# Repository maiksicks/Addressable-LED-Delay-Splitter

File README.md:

# Addressable LED Delay Splitter (WS2812B / SK6812)

This project implements a "delay splitter" for addressable LED strips (WS2812B / SK6812) using an [ATtiny406](https://www.microchip.com/en-us/product/attiny406) microcontroller.
The device should work for all 800 kHz LED strips that only use one data line.

> Inspired by [WS2812B Delay Splitter](https://hackaday.io/project/8181-ws2812b-delay-splitter) that uses a [CMIC](https://en.wikipedia.org/wiki/Configurable_mixed-signal_IC) for this task.

> [!NOTE]
> More images are available in the [Gallery](./docs/Gallery.md). Including a short demo video showing the device in action.

## Description

The splitter takes a single LED data stream as input and provides two outputs:

- **Primary output**: This channel outputs the first N pixels of the input stream, where N is the configured pixel number.

- **Secondary output**: This channel outputs the remaining pixels of the input stream after the first N pixels.

### Basic use-case

- `pixel delay = 3`
    ```
                                 +- (1) - (2) - (3)
    [Controller] --- [Splitter] -+
                                 +- (4) - (5) - (6)
    ```

- `pixel delay = 3` and `primary passthrough = on`
    ```
                                 +- (1) - (2) - (3) - (4) - (5) - (6)
    [Controller] --- [Splitter] -+
                                 +- (4) - (5) - (6)
    ```

- Chaining
    ```
                                 +- (1) - (2) - (3)
    [Controller] --- [Splitter] -+
                                 +- [Splitter] ...
    ```
    ```
    [Controller] --- (1) - (2) - (3) --- [Splitter] ...
    ```

### How it works

Due to the high frequency of the WS2812B protocol (800kHz, 1.25µs per bit), the splitter uses many hardware features of the ATtiny406 to achieve the required timing:

- **Event System**
  Distribute the different signals (data input and control pin) to the various peripherals w(mostly) without CPU intervention.

- **CCL (Configurable Custom Logic)**
  Look-up tables (LUTs) are used to asynchronously route the input data stream to the outputs.

  - `Output_1 = Input_1 AND NOT Control_Pin`
  - `Output_2 = Input_1 AND Control_Pin`

- **TCA0 (Bit Counter)**
  Counts the number of bits / rising edges / events received via the event system. When the configured number of bits (delay) is reached, the control pin is switched to route the data to output 2.

- **TCB0 (Timeout Timer)**
  When the control pin is switched to output 2, this timer is started. If no rising edges are detected for a certain amount of time (indicating the reset condition of the WS2812B), the control pin is switched back to output 1.

## Configuration

The device can be configured via jumpers or by hardcoding values in `config.hpp`.

### Jumper configuration

There are 8 jumpers available to configure the pixel delay. The delay can be set from 0 to 255 pixels.

There is an additional jumper to change from RGB mode (24 bits per pixel) to RGBW mode (32 bits per pixel).

### Hardcoded configuration

The following parameters can be hardcoded in `config.hpp`:

- `PIXEL_DELAY` - Number of pixels to delay the output
- `RGBW_MODE` - Enable RGBW mode (32 bits per pixel instead of 24)
- `BITS_PER_PIXEL` - Number of bits per pixel (24 for RGB, 32 for RGBW)
- `SWAP_OUTPUTS` - Swap the primary and secondary outputs (output 1 and output 2)
- `PRIMARY_OUTPUT_PASSTHROUGH` - Enable passthrough of the primary output. When enabled, the primary output will not be turned off when the secondary output is active.
- `DISABLE_OUTPUT_1` and `DISABLE_OUTPUT_2` - Self-explanatory :)
- `LED_RESET_TIMEOUT` - Duration (in microseconds) to detect the reset condition of the WS2812B. The default is 50µs, which is a safe value for up to ~800kHz data rates.

Special parameters:

- `FORCE_SHORTED_CONTROL_PIN` - Forces the _shorted configuration pin mode_ to be enabled. This mode will be automatically enabled if jumper "128" is used. The control signal will then be inverted internally instead of setting the pin HIGH and LOW. 
  _Background: This mode had to be introduced because the hardware design of the splitter (revision 1) already had all Port B pins used for the configuration jumpers. The Event System only supports Port B pins as event generators on `ASYNCCH1`._

### Operation voltage

The device contains an onboard voltage regulator that can accept input voltages up to 30V (absolute maximum rating). Therefore, the recommend input voltages are 12V and 24V.

It is also possible to power the device with 5V. However, in this case, the voltage regulator will not be able to provide a stable 5V output for the ATtiny406. It may be a good idea to remove the voltage regulator and connect the 5V pin directly to the VCC pin.

### Flashing

The project can be built and flashed using [PlatformIO](https://platformio.org/).

For flashing, an UPDI programmer is required. 
You can also build a simple UPDI programmer using an Arduino Uno/Nano with ATmega328P:

1. Download the [jtag2updi repository](https://github.com/ElTangas/jtag2updi).
2. Rename the `source` folder to `jtag2updi` (otherwise Arduino IDE will not open it).
3. Open the `jtag2updi.ino` file using the Arduino IDE.
4. Connect the Arduino, select the correct board and port in the Arduino IDE, and upload the sketch.

After this, you can connect pin 6 of the Arduino to the UPDI pin of the ATtiny406, and use PlatformIO to flash the splitter firmware.

## Limitations

There is a maximum amount of leds that can be connected to a single data line. This limit is determined by the data rate of the LEDs. The formula to calculate the maximum number of LEDs is:

`N = ( (1 / f) - T_reset ) / ( B / R )`

Where:
- `N` = maximum number of LEDs
- `f` = frames per second (e.g. 60Hz)
- `T_reset` = reset time of the LEDs (e.g. 50µs)
- `B` = bits per pixel (e.g. 24 for RGB, 32 for RGBW)
- `R` = data rate in bits per second (e.g. 800,000 bps)

Example:
- With 60 Hz and RGB LEDs: up to 553 LEDs
- With 60 Hz and RGBW LEDs: up to 415 LEDs

- With 30 Hz and RGB LEDs: up to 1109 LEDs
- With 30 Hz and RGBW LEDs: up to 832 LEDs

## Ordering PCBs

Read the [README](./kicad/Addressable_LED_Delay_Splitter/README.md) in the `kicad` folder for details on the PCB design and order.

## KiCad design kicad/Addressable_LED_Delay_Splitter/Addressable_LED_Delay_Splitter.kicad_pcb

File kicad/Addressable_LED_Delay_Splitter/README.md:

# Addressable LED Delay Splitter (PCB)

This folder contains the [KiCad](https://kicad.org/) project for the Addressable LED Delay Splitter PCB.

## Production files

Production files can be found in the `jlcpcb/production_files` folder.
These files were generated by the [KiCAD JLCPCB tools plugin](https://github.com/bouni/kicad-jlcpcb-tools).

It should be possible to upload the GERBER archive to other PCB manufacturers as well, but this has not been tested.

The BOM and CPL files are in the format required by [JLCPCB](https://jlcpcb.com/).

It may be required to check and adjust the part numbers before ordering, because parts are from time to time replaced or go out of stock.

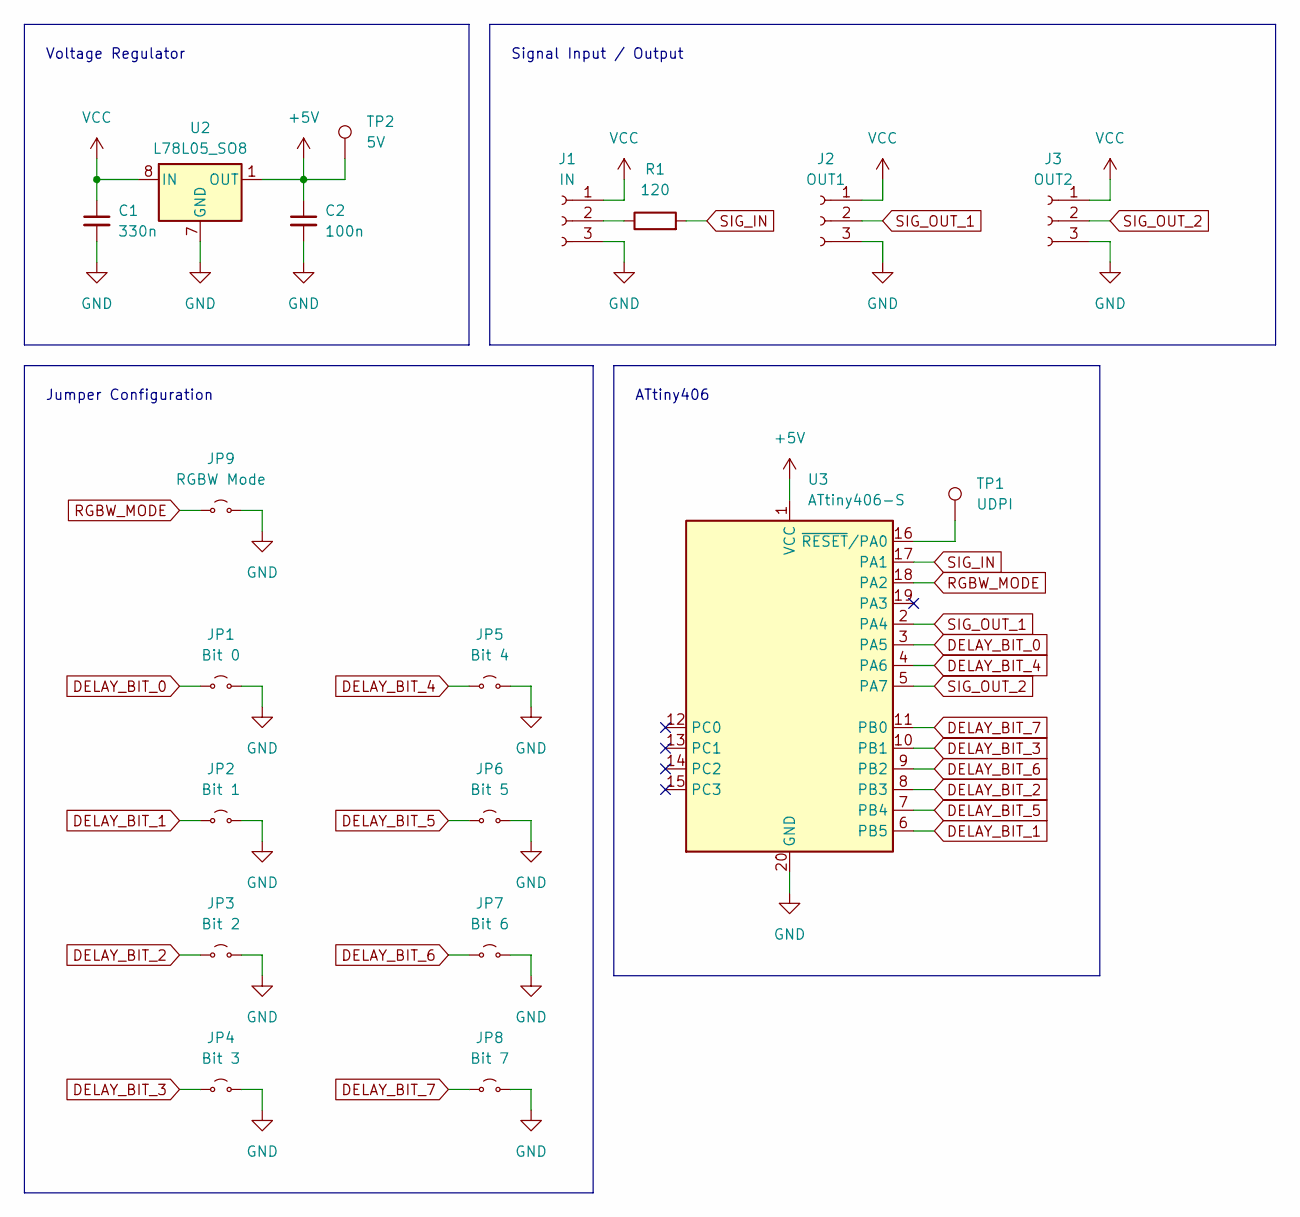
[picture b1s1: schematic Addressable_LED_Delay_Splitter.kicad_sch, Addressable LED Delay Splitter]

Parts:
C1: 330n; C_0805_2012Metric; LCSC C49678
C2: 100n; C_0805_2012Metric; LCSC C13967
J1: IN; ARGB_Solder_Header
J2: OUT1; ARGB_Solder_Header
J3: OUT2; ARGB_Solder_Header
JP1: Bit 0; SolderJumper-2_P1.3mm_Open_RoundedPad1.0x1.5mm
JP2: Bit 1; SolderJumper-2_P1.3mm_Open_RoundedPad1.0x1.5mm
JP3: Bit 2; SolderJumper-2_P1.3mm_Open_RoundedPad1.0x1.5mm
JP4: Bit 3; SolderJumper-2_P1.3mm_Open_RoundedPad1.0x1.5mm
JP5: Bit 4; SolderJumper-2_P1.3mm_Open_RoundedPad1.0x1.5mm
JP6: Bit 5; SolderJumper-2_P1.3mm_Open_RoundedPad1.0x1.5mm
JP7: Bit 6; SolderJumper-2_P1.3mm_Open_RoundedPad1.0x1.5mm
JP8: Bit 7; SolderJumper-2_P1.3mm_Open_RoundedPad1.0x1.5mm
JP9: RGBW Mode; SolderJumper-2_P1.3mm_Open_RoundedPad1.0x1.5mm
R1: 120; R_0805_2012Metric; LCSC C17437
TP1: UDPI; TestPoint_Pad_D1.0mm
TP2: 5V; TestPoint_Pad_D1.0mm
U2: L78L05_SO8; SOIC-8_3.9x4.9mm_P1.27mm; LCSC C7543
U3: ATtiny406-S; SOIC-20W_7.5x12.8mm_P1.27mm; LCSC C1338099

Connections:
+5V: C2.1, TP2.1, U2.1 (OUT), U3.1 (VCC)
DELAY_BIT_0: JP1.1 (A), U3.3 (PA5)
DELAY_BIT_1: JP2.1 (A), U3.6 (PB5)
DELAY_BIT_2: JP3.1 (A), U3.8 (PB3)
DELAY_BIT_3: JP4.1 (A), U3.10 (PB1)
DELAY_BIT_4: JP5.1 (A), U3.4 (PA6)
DELAY_BIT_5: JP6.1 (A), U3.7 (PB4)
DELAY_BIT_6: JP7.1 (A), U3.9 (PB2)
DELAY_BIT_7: JP8.1 (A), U3.11 (PB0)
GND: C1.2, C2.2, J1.3, J2.3, J3.3, JP1.2 (B), JP2.2 (B), JP3.2 (B), JP4.2 (B), JP5.2 (B), JP6.2 (B), JP7.2 (B), JP8.2 (B), JP9.2 (B), U2.2 (GND), U2.3 (GND), U2.6 (GND), U2.7 (GND), U3.20 (GND)
unnamed: J1.2, R1.1
unnamed: TP1.1, U3.16 (~RESET/PA0)
RGBW_MODE: JP9.1 (A), U3.18 (PA2)
SIG_IN: R1.2, U3.17 (PA1)
SIG_OUT_1: J2.2, U3.2 (PA4)
SIG_OUT_2: J3.2, U3.5 (PA7)
VCC: C1.1, J1.1, J2.1, J3.1, U2.8 (IN)

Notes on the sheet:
ATtiny406
Signal Input / Output
Voltage Regulator
Jumper Configuration

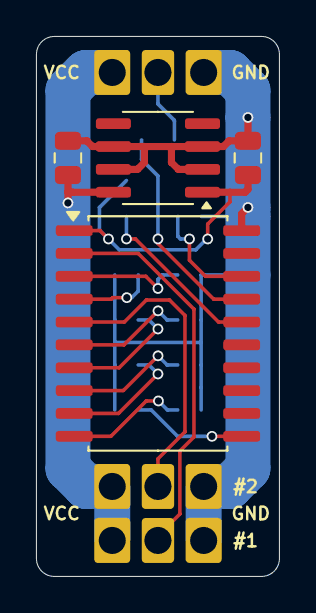
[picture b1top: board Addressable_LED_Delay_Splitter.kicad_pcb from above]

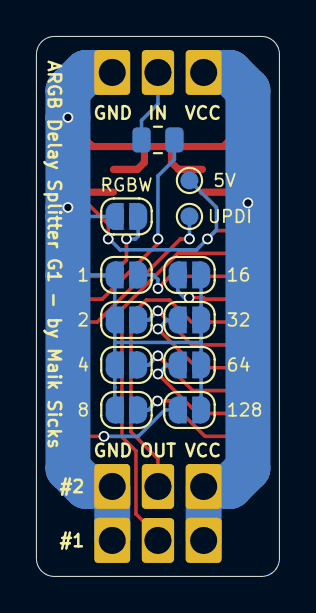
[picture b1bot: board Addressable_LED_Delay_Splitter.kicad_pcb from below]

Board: 2 copper layers, 13.5 x 30.0 mm, 19 parts (12 on the bottom side), 17 nets.

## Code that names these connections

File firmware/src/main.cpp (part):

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 * WS2812B Signal Splitter for ATTiny406
 *
 * Splits an incoming WS2812B signal into two outputs based on pixel count.
 * - First N pixels go to Output 1 (PA4 / LUT0-OUT)
 * - Remaining pixels go to Output 2 (PA7 / LUT1-OUT)
 */


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 * Reads configuration from GPIO pins if READ_CONFIG_FROM_JUMPERS is defined,
 * otherwise uses hardcoded values.
 *
 * Also detects if PB0 is shorted to ground and adjusts control logic accordingly.
 *
 * Delay pixel count (8-bit value):
 *   PA5: Bit 0 (LSB)
 *   PB5: Bit 1
 *   PB3: Bit 2
 *   PB1: Bit 3
 *   PA6: Bit 4
 *   PB4: Bit 5
 *   PB2: Bit 6
 *   PB0: Bit 7 (MSB)
 *
 * RGBW mode:
 *   PA2: RGBW enable (1 = 32 bits/pixel, 0 = 24 bits/pixel)
 *
 * Pins are read with pull-ups enabled:
 *   - Grounded pin = 1 (jumper installed)
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    // Small delay to let pull-ups stabilize
    _delay_us(100);

    // Read RGBW mode from PA2
    bool rgbw_mode = !(PORTA.IN & PIN2_bm);

    if (rgbw_mode) {
      bits_per_pixel = BITS_PER_PIXEL_RGBW;
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    if (!(PORTB.IN & PIN0_bm)) pixel_delay |= (1 << 7);  // Bit 7

    #ifndef FORCE_SHORTED_CONTROL_PIN
      // Check if PB0 is shorted to ground
      if (pixel_delay & (1 << 7)) {
        controlPinShorted = true;
      }
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    // Use hardcoded configuration values

    #ifndef FORCE_SHORTED_CONTROL_PIN
      // Check if PB0 is shorted to ground by configuring it as input with pull-up and reading its state
      PORTB.DIRCLR = PIN0_bm;
      PORTB.PIN0CTRL = PORT_PULLUPEN_bm;

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 * Configure GPIO pins
 */
void setupPins() {
  // PA1: Input (WS2812B data input)
  PORTA.DIRCLR = PIN1_bm;

  // PA4 and PA7 direction is controlled by CCL when OUTEN is enabled
  // But we set them as outputs for clarity
  PORTA.DIRSET = PIN4_bm | PIN7_bm;

  // PB0: Control pin for output switching
  if (controlPinShorted) {
    // Use PB0 as input. Toggle invert flag to trigger events.
    PORTB.DIRCLR = PIN0_bm;
  } else {
    // Use PB0 as output. Toggle output to trigger events.
    PORTB.DIRSET = PIN0_bm;
    PORTB.OUTSET = PIN0_bm;
  }
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/**
 * Configure the Event System
 *
 * Routes PA1 signal to:
 * - Both LUTs via Async Event Channel 0 (for signal buffering)
 * - TCA0 via Sync Event Channel 0 (for hardware bit counting)
 *
 * Routes PB0 signal to:
 * - Both LUTs via Async Event Channel 1 (for output control)
 */
void setupEventSystem() {
  // Async Channel 0: PA1 (data signal) for both LUTs
  EVSYS.ASYNCCH0 = EVSYS_ASYNCCH0_PORTA_PIN1_gc;

  // Async Channel 1: PB0 (control signal) for both LUTs
  EVSYS.ASYNCCH1 = EVSYS_ASYNCCH1_PORTB_PIN0_gc;

  // Route Async Channel 0 to both LUT0 and LUT1 Event 0 inputs
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  EVSYS.ASYNCUSER4 = EVSYS_ASYNCUSER4_ASYNCCH1_gc;  // LUT0 E1 <- CH1 (control)
  EVSYS.ASYNCUSER5 = EVSYS_ASYNCUSER5_ASYNCCH1_gc;  // LUT1 E1 <- CH1 (control)

  // Sync Channel 0: PA1 (data signal) for TCA0
  EVSYS.SYNCCH0 = EVSYS_SYNCCH0_PORTA_PIN1_gc;

  // Route Sync Channel 0 to TCA0 for event counting
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 * Configure the CCL (Configurable Custom Logic)
 *
 * Two LUTs are configured to control the outputs based on the data and control signals:
 * - LUT0 controls Output 1 (PA4)
 * - LUT1 controls Output 2 (PA7)
 *
 * Both LUTs use the same inputs:
 * - Input 0: Event 0 (data signal from PA1)
 * - Input 1: Event 1 (control signal from PB0)
 * - Input 2: Masked (forced to 0)
 */
void setupCCL() {
  // Disable CCL while configuring
  CCL.CTRLA = 0;

  // LUT0 Configuration (Output 1 - PA4)
  CCL.LUT0CTRLB = CCL_INSEL0_EVENT0_gc | CCL_INSEL1_EVENT1_gc;
  CCL.LUT0CTRLC = CCL_INSEL2_MASK_gc;

  // TRUTH0 table configuration
  CCL.TRUTH0 = TRUTH0_DATA;

  // Enable LUT0 with output to pin PA4
  CCL.LUT0CTRLA = CCL_OUTEN_bm | CCL_ENABLE_bm;

  // LUT1 Configuration (Output 2 - PA7)
  CCL.LUT1CTRLB = CCL_INSEL0_EVENT0_gc | CCL_INSEL1_EVENT1_gc;
  CCL.LUT1CTRLC = CCL_INSEL2_MASK_gc;

  // TRUTH1 table configuration
  CCL.TRUTH1 = TRUTH1_DATA;

  // Enable LUT1 with output to pin PA7
  CCL.LUT1CTRLA = CCL_OUTEN_bm | CCL_ENABLE_bm;

  // Enable the CCL peripheral
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 * Setup pin interrupts
 */
void setupPinInterrupts() {
  // Configure PA1 for rising edge interrupt,
  // used to restart timeout timer on data activity.
  PORTA.PIN1CTRL = PORT_ISC_RISING_gc;
}
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/**
 * Port A Pin Change Interrupt
 *
 * Triggered on rising edge of PA1 (WS2812B data input)
 * Resets the timeout timer to prevent false reset detection during active data
 */
ISR(PORTA_PORT_vect, ISR_NAKED) {
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
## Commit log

2026-02-28 add readme
2026-02-28 setup workspace
2026-02-28 firmware: initial commit
2026-02-28 update readme
    - add compatibility info
    - add inspiration
    - update formatting
2026-02-28 pcb: initial commit
2026-02-28 add assets
2026-02-28 firmware: fix jumper bit
2026-02-28 docs: clarify LED connection limits and provide calculation formula
2026-02-28 docs: cleanup and fix image paths
2026-02-28 firmware: fix macro name for jumper config
2026-02-28 docs: add gallery
2026-02-28 docs: reupload demo video
    Replaced demo video link with a GitHub asset link.
2026-02-28 docs: add video description
2026-02-28 docs: add section about operation voltages
2026-03-19 firmware: add configuration sample when using UPDI friend
